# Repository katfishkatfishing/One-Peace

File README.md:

# One-Peace 🏴‍☠️
>Our plan for Third Space Hack Club - Week 2!

A locked box that refuses to open until brought to a specific geographic coordinate that can be determined through various puzzles.

ARG GitHub here:
[https://github.com/katfishkatfishing/Eye-of-God](https://github.com/katfishkatfishing/Eye-of-God)

## Overview
An arg inspired puzzle, alien-y sci-fi themed reverse geocache box. At first we started with the theme of treasure, then thought of geocaches. But those were already a thing, and we wanted our project to be unique so we did this reverse geocache, where you bring the box to the place then only it opens.
The ARG itself is cosmic horror themed.
To put it short, it's a box that only opens if you bring it to the specific coordinates (approximately).

### <ins>The Box</ins>
<ul style="margin-top: -5px; margin-bottom: 0; padding-left: 10px">
  <p style="margin-bottom: 5px">
    <b>GPS Tracking</b>
    <ul style="padding-left: 45px">
      <p style="text-indent: -24px; margin-bottom: 5px">
        <b>GPS Receiver Module:</b> An internal GPS receiver reads satellite signals to calculate latitude, longitude and keep track of its current location.</p>
      <p style="text-indent: -24px; margin-bottom: 5px">
        <b>Geofencing & Distance Logic:</b> The internal microcontroller runs algorithms to calculate the distance between the box's current coordinates and the pre-programmed target coordinates.</p>
      <p style="text-indent: -24px; margin-bottom: 20px">
        <b>Proximity Threshold:</b> The box opens once it is within a designated radius.</p>
    </ul>
  </p>
</ul>
<ul style="margin-top: 0; margin-bottom: 0; padding-left: 10px">
  <p style="margin-bottom: 5px">
    <b>Locking Mechanism</b>
    <ul style="padding-left: 45px">
      <p style="text-indent: -24px; margin-bottom: 5px">
        <b>Electronic Lock:</b> A motorized latch, driven by a micro servo motor that secures the lid mechanism.</p>
    </ul>
  </p>
</ul>
<ul style="margin-top: 0; margin-bottom: 0; padding-left: 10px">
  <p style="margin-bottom: 5px">
    <b>ARG Puzzle</b>
    <ul style="padding-left: 45px">
      <p style="text-indent: -24px; margin-bottom: 5px">
        <b>Puzzles!:</b> Clues that lead to more clues that lead to the destination, to witness the <i><b>"One Peace"</b></i> <i>(ps. the puzzles are ciphers)<i></p>
    </ul>
  </p>
</ul>

## PCB
Let's take a look at what is inside!
<table>
  <tr>
    <td align="center">
      Schematic<br>
      <br>
    </td>
    <td align="center">
      PCB Routing<br>
      <br>
    </td>
  </tr>
</table>

Now, let's take a look outside!
<table>
  <tr>
    <td align="center">
      <br>
    </td>
    <td align="center">
      <br>
    </td>
  </tr>
</table>

## BOM 💹
| Reference          | Qty | Value                         | DNP | Exclude from BOM | Exclude from Board | Footprint                                                                                  | Datasheet                                                                                            |
| ------------------ | --- | ----------------------------- | --- | ---------------- | ------------------ | ------------------------------------------------------------------------------------------ | ---------------------------------------------------------------------------------------------------- |
| C1                 | 1   | 470uF                         |     |                  |                    | Capacitor_Tantalum_SMD:CP_EIA-7343-43_Kemet-X_HandSolder                                   |                                                                                                      |
| C3,C9,C10          | 3   | 10uF                          |     |                  |                    | Capacitor_SMD:C_0603_1608Metric_Pad1.08x0.95mm_HandSolder                                  |                                                                                                      |
| C4,C7              | 2   | 0.1uF                         |     |                  |                    | Capacitor_SMD:C_0402_1005Metric_Pad0.74x0.62mm_HandSolder                                  |                                                                                                      |
| C5,C12,C13,C14,C15 | 5   | 22uF                          |     |                  |                    | Capacitor_SMD:C_0603_1608Metric_Pad1.08x0.95mm_HandSolder                                  |                                                                                                      |
| C6                 | 1   | 1uF                           |     |                  |                    | Capacitor_SMD:C_0603_1608Metric_Pad1.08x0.95mm_HandSolder                                  |                                                                                                      |
| C8                 | 1   | 100nF                         |     |                  |                    | Capacitor_SMD:C_0402_1005Metric_Pad0.74x0.62mm_HandSolder                                  |                                                                                                      |
| C11                | 1   | 10pF                          |     |                  |                    | Capacitor_SMD:C_0402_1005Metric_Pad0.74x0.62mm_HandSolder                                  |                                                                                                      |
| D3,D4,D5           | 3   | LED                           |     |                  |                    | LED_SMD:LED_0603_1608Metric_Pad1.05x0.95mm_HandSolder                                      |                                                                                                      |
| J1                 | 1   | USB_C_Receptacle_USB2.0_16P   |     |                  |                    | Connector_USB:USB_C_Receptacle_GCT_USB4085                                                 | https://www.usb.org/sites/default/files/documents/usb_type-c.zip                                     |
| J2                 | 1   | U.FL                          |     |                  |                    | U.FL_Molex_MCRF_73412-0110_Vertical:U.FL_Molex_MCRF_73412-0110_Vertical                    | https://wmsc.lcsc.com/wmsc/upload/file/pdf/v2/lcsc/2208151830_BAT-WIRELESS-BWU-FL-IPEX1_C5137195.pdf |
| J3                 | 1   | Conn_01x02                    |     |                  |                    | Connector_PinHeader_2.54mm:PinHeader_1x02_P2.54mm_Vertical                                 |                                                                                                      |
| L1                 | 1   | 1uH                           |     |                  |                    | Inductor_SMD:L_APV_ANR4030                                                                 |                                                                                                      |
| LCD1               | 1   | HS280S010B                    |     |                  |                    | lcsc_shared_footprints:C2939938_LCD-TH_HS280S010B                                          | https://wmsc.lcsc.com/wmsc/upload/file/pdf/v2/lcsc/2401291705_HS-HS280S010B_C2939938.pdf             |
| M1                 | 1   | Motor_Servo                   |     |                  |                    | Connector_PinHeader_2.54mm:PinHeader_1x03_P2.54mm_Vertical                                 | http://forums.parallax.com/uploads/attachments/46831/74481.png                                       |
| R6,R7,R8           | 3   | 470R                          |     |                  |                    | Resistor_SMD:R_0402_1005Metric_Pad0.72x0.64mm_HandSolder                                   |                                                                                                      |
| R9,R17             | 2   | 10k                           |     |                  |                    | Resistor_SMD:R_0603_1608Metric_Pad0.98x0.95mm_HandSolder                                   |                                                                                                      |
| R10                | 1   | 2k                            |     |                  |                    | Resistor_SMD:R_0603_1608Metric_Pad0.98x0.95mm_HandSolder                                   |                                                                                                      |
| R13,R14            | 2   | 5.1k                          |     |                  |                    | Resistor_SMD:R_0603_1608Metric_Pad0.98x0.95mm_HandSolder                                   |                                                                                                      |
| R18                | 1   | 0R                            |     |                  |                    | Resistor_SMD:R_0402_1005Metric_Pad0.72x0.64mm_HandSolder                                   |                                                                                                      |
| R19                | 1   | 1.6M                          |     |                  |                    | Resistor_SMD:R_0603_1608Metric_Pad0.98x0.95mm_HandSolder                                   |                                                                                                      |
| R20                | 1   | 39k                           |     |                  |                    | Resistor_SMD:R_0603_1608Metric_Pad0.98x0.95mm_HandSolder                                   |                                                                                                      |
| R21                | 1   | 1M                            |     |                  |                    | Resistor_SMD:R_0603_1608Metric                                                             |                                                                                                      |
| R22                | 1   | 180k                          |     |                  |                    | Resistor_SMD:R_0603_1608Metric_Pad0.98x0.95mm_HandSolder                                   |                                                                                                      |
| SW4                | 1   | SW_Push                       |     |                  |                    | Button_Switch_SMD:SW_SPST_B3U-1000P                                                        |                                                                                                      |
| U1                 | 1   | AMS1117-3.3                   |     |                  |                    | Package_TO_SOT_SMD:SOT-223-3_TabPin2                                                       | http://www.advanced-monolithic.com/pdf/ds1117.pdf                                                    |
| U2                 | 1   | NEO-6M-0-001_C32413118        |     |                  |                    | lcsc_shared_footprints:C32413118_SMD                                                       | None                                                                                                 |
| U3                 | 1   | TPS63020DSJR                  |     |                  |                    | lcsc_shared_footprints:C15483_VSON-14_L4_0-W3_0-P0_50-BL-EP_TI_DSJ                         | https://www.lcsc.com/datasheet/lcsc_datasheet_1809200040_Texas-Instruments-TPS63020DSJR_C15483.pdf   |
| U4                 | 1   | MCP73871-2CC                  |     |                  |                    | Package_DFN_QFN:QFN-20-1EP_4x4mm_P0.5mm_EP2.5x2.5mm                                        | http://www.mouser.com/ds/2/268/22090a-52174.pdf                                                      |
| U5                 | 1   | ESP32-S31-WROOM-3_C9900281993 |     |                  |                    | lcsc_shared_footprints:C9900281993_COMM-SMD_99P-L33_0-W26_0-P0_85_ESP32-S31-MINI-1-H16R16V | None                                                                                                 |

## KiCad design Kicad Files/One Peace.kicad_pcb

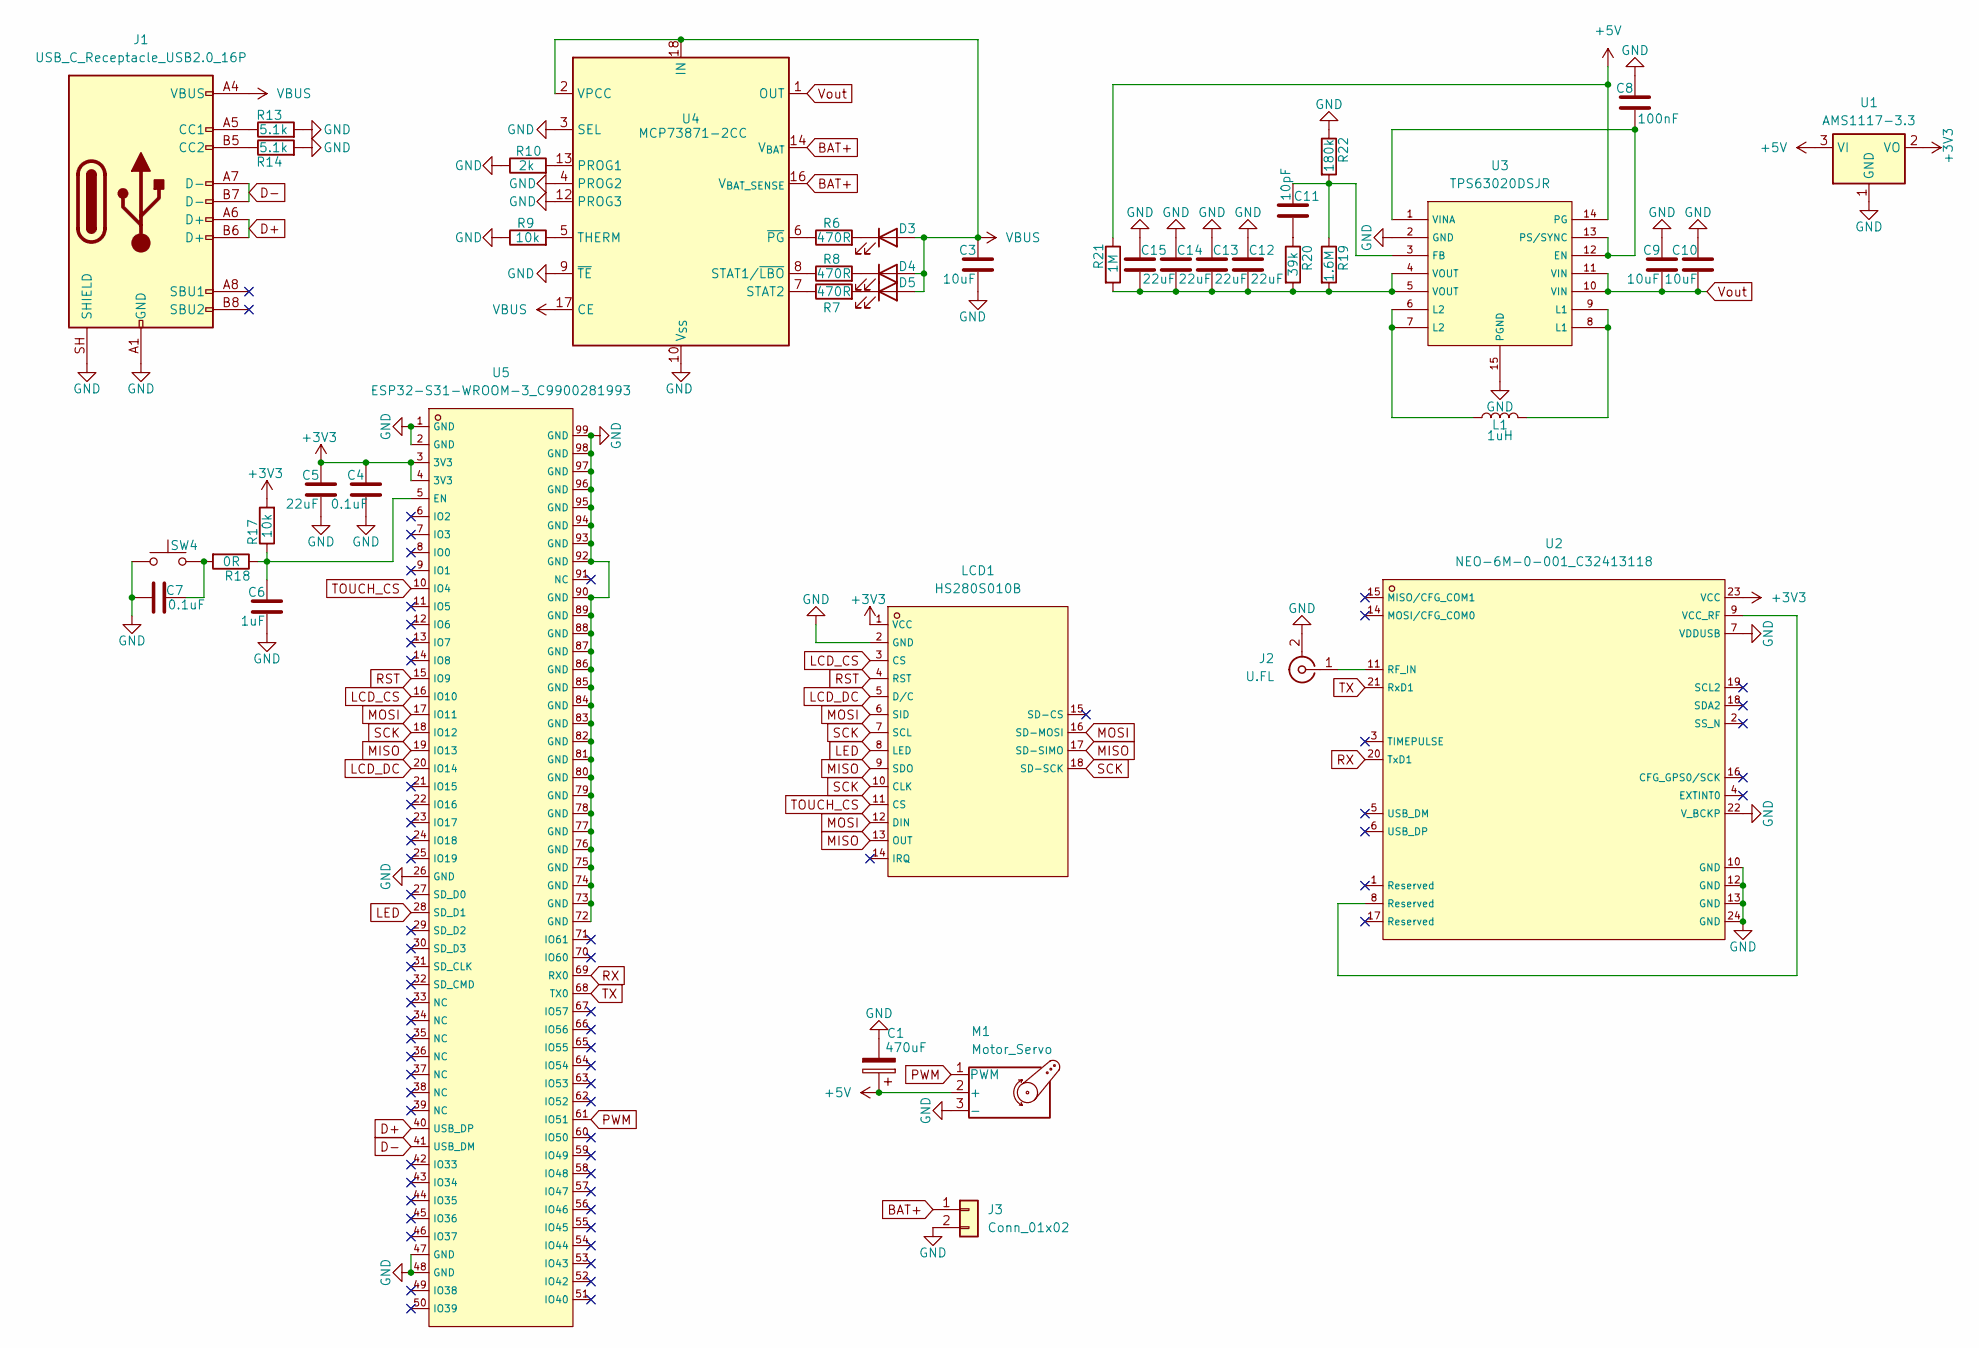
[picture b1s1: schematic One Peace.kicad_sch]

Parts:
C1: 470uF; CP_EIA-7343-43_Kemet-X_HandSolder
C3, C9, C10: 10uF; C_0603_1608Metric_Pad1.08x0.95mm_HandSolder
C4, C7: 0.1uF; C_0402_1005Metric_Pad0.74x0.62mm_HandSolder
C5, C12, C13, C14, C15: 22uF; C_0603_1608Metric_Pad1.08x0.95mm_HandSolder
C6: 1uF; C_0603_1608Metric_Pad1.08x0.95mm_HandSolder
C8: 100nF; C_0402_1005Metric_Pad0.74x0.62mm_HandSolder
C11: 10pF; C_0402_1005Metric_Pad0.74x0.62mm_HandSolder
D3, D4, D5: LED; LED_0603_1608Metric_Pad1.05x0.95mm_HandSolder
J1: USB_C_Receptacle_USB2.0_16P; USB_C_Receptacle_GCT_USB4085
J2: U.FL; U.FL_Molex_MCRF_73412-0110_Vertical; LCSC C5137195
J3: Conn_01x02; PinHeader_1x02_P2.54mm_Vertical
L1: 1uH; L_APV_ANR4030
LCD1: HS280S010B; C2939938_LCD-TH_HS280S010B; LCSC C2939938
M1: Motor_Servo; PinHeader_1x03_P2.54mm_Vertical
R6, R7, R8: 470R; R_0402_1005Metric_Pad0.72x0.64mm_HandSolder
R9, R17: 10k; R_0603_1608Metric_Pad0.98x0.95mm_HandSolder
R10: 2k; R_0603_1608Metric_Pad0.98x0.95mm_HandSolder
R13, R14: 5.1k; R_0603_1608Metric_Pad0.98x0.95mm_HandSolder
R18: 0R; R_0402_1005Metric_Pad0.72x0.64mm_HandSolder
R19: 1.6M; R_0603_1608Metric_Pad0.98x0.95mm_HandSolder
R20: 39k; R_0603_1608Metric_Pad0.98x0.95mm_HandSolder
R21: 1M; R_0603_1608Metric
R22: 180k; R_0603_1608Metric_Pad0.98x0.95mm_HandSolder
SW4: SW_Push; SW_SPST_B3U-1000P
U1: AMS1117-3.3; SOT-223-3_TabPin2
U2: NEO-6M-0-001_C32413118; C32413118_SMD; LCSC C32413118
U3: TPS63020DSJR; C15483_VSON-14_L4_0-W3_0-P0_50-BL-EP_TI_DSJ; LCSC C15483
U4: MCP73871-2CC; QFN-20-1EP_4x4mm_P0.5mm_EP2.5x2.5mm
U5: ESP32-S31-WROOM-3_C9900281993; C9900281993_COMM-SMD_99P-L33_0-W26_0-P0_85_ESP32-S31-MINI-1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; LCSC C9900281993

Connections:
+3V3: C4.1, C5.1, LCD1.1 (VCC), R17.2, U1.2 (VO), U2.23 (VCC), U5.3 (3V3), U5.4 (3V3)
+5V: C1.1, M1.2 (+), R21.1, U1.3 (VI), U3.14 (PG)
BAT+: J3.1, U4.14 (V_{BAT}), U4.15 (V_{BAT}), U4.16 (V_{BAT_SENSE})
D+: J1.A6 (D+), J1.B6 (D+), U5.40 (USB_DP)
D-: J1.A7 (D-), J1.B7 (D-), U5.41 (USB_DM)
GND: C1.2, C3.2, C4.2, C5.2, C6.2, C7.1, C8.1, C9.1, C10.1, C12.1, C13.1, C14.1, C15.1, J1.A1 (GND), J1.A12 (GND), J1.B1 (GND), J1.B12 (GND), J1.SH (SHIELD), J2.2 (Ext), J3.2, LCD1.2 (GND), M1.3 (-), R9.1, R10.1, R13.2, R14.2, R22.1, SW4.2, U1.1 (GND), U2.7 (VDDUSB), U2.10 (GND), U2.12 (GND), U2.13 (GND), U2.22 (V_BCKP), U2.24 (GND), U3.2 (GND), U3.15 (PGND), U4.3 (SEL), U4.4 (PROG2), U4.9 (~TE), U4.10 (V_{SS}), U4.11 (V_{SS}), U4.12 (PROG3), U4.21 (V_{SS}), U5.1 (GND), U5.2 (GND), U5.26 (GND), U5.47 (GND), U5.48 (GND), U5.72 (GND), U5.73 (GND), U5.74 (GND), U5.75 (GND), U5.76 (GND), U5.77 (GND), U5.78 (GND), U5.79 (GND), U5.80 (GND), U5.81 (GND), U5.82 (GND), U5.83 (GND), U5.84 (GND), U5.85 (GND), U5.86 (GND), U5.87 (GND), U5.88 (GND), U5.89 (GND), U5.90 (GND), U5.92 (GND), U5.93 (GND), U5.94 (GND), U5.95 (GND), U5.96 (GND), U5.97 (GND), U5.98 (GND), U5.99 (GND)
LCD_CS: LCD1.3 (CS), U5.16 (IO10)
LCD_DC: LCD1.5 (D/C), U5.20 (IO14)
LED: LCD1.8 (LED), U5.28 (SD_D1)
MISO: LCD1.9 (SDO), LCD1.13 (OUT), LCD1.17 (SD-SIMO), U5.19 (IO13)
MOSI: LCD1.6 (SID), LCD1.12 (DIN), LCD1.16 (SD-MOSI), U5.17 (IO11)
unnamed: C7.2, R18.2, SW4.1
unnamed: C11.2, R20.1
unnamed: C12.2, C13.2, C14.2, C15.2, R19.2, R20.2, R21.2, U3.4 (VOUT), U3.5 (VOUT)
unnamed: D3.1 (K), R6.2
unnamed: D4.1 (K), R8.2
unnamed: D5.1 (K), R7.2
unnamed: J1.A5 (CC1), R13.1
unnamed: J1.B5 (CC2), R14.1
unnamed: J2.1 (In), U2.11 (RF_IN)
unnamed: L1.1, U3.6 (L2), U3.7 (L2)
unnamed: L1.2, U3.8 (L1), U3.9 (L1)
unnamed: U2.8 (Reserved), U2.9 (VCC_RF)
unnamed: C8.2, U3.1 (VINA), U3.12 (EN), U3.13 (PS/SYNC)
unnamed: C11.1, R19.1, R22.2, U3.3 (FB)
unnamed: R10.2, U4.13 (PROG1)
unnamed: R8.1, U4.8 (STAT1/~LBO)
unnamed: R7.1, U4.7 (STAT2)
unnamed: R9.2, U4.5 (THERM)
unnamed: R6.1, U4.6 (~PG)
unnamed: C6.1, R17.1, R18.1, U5.5 (EN)
PWM: M1.1 (PWM), U5.61 (IO51)
RST: LCD1.4 (RST), U5.15 (IO9)
RX: U2.20 (TxD1), U5.69 (RX0)
SCK: LCD1.7 (SCL), LCD1.10 (CLK), LCD1.18 (SD-SCK), U5.18 (IO12)
TOUCH_CS: LCD1.11 (CS), U5.10 (IO4)
TX: U2.21 (RxD1), U5.68 (TX0)
VBUS: C3.1, D3.2 (A), D4.2 (A), D5.2 (A), J1.A4 (VBUS), J1.A9 (VBUS), J1.B4 (VBUS), J1.B9 (VBUS), U4.2 (VPCC), U4.17 (CE), U4.18 (IN), U4.19 (IN)
Vout: C9.2, C10.2, U3.10 (VIN), U3.11 (VIN), U4.1 (OUT), U4.20 (OUT)

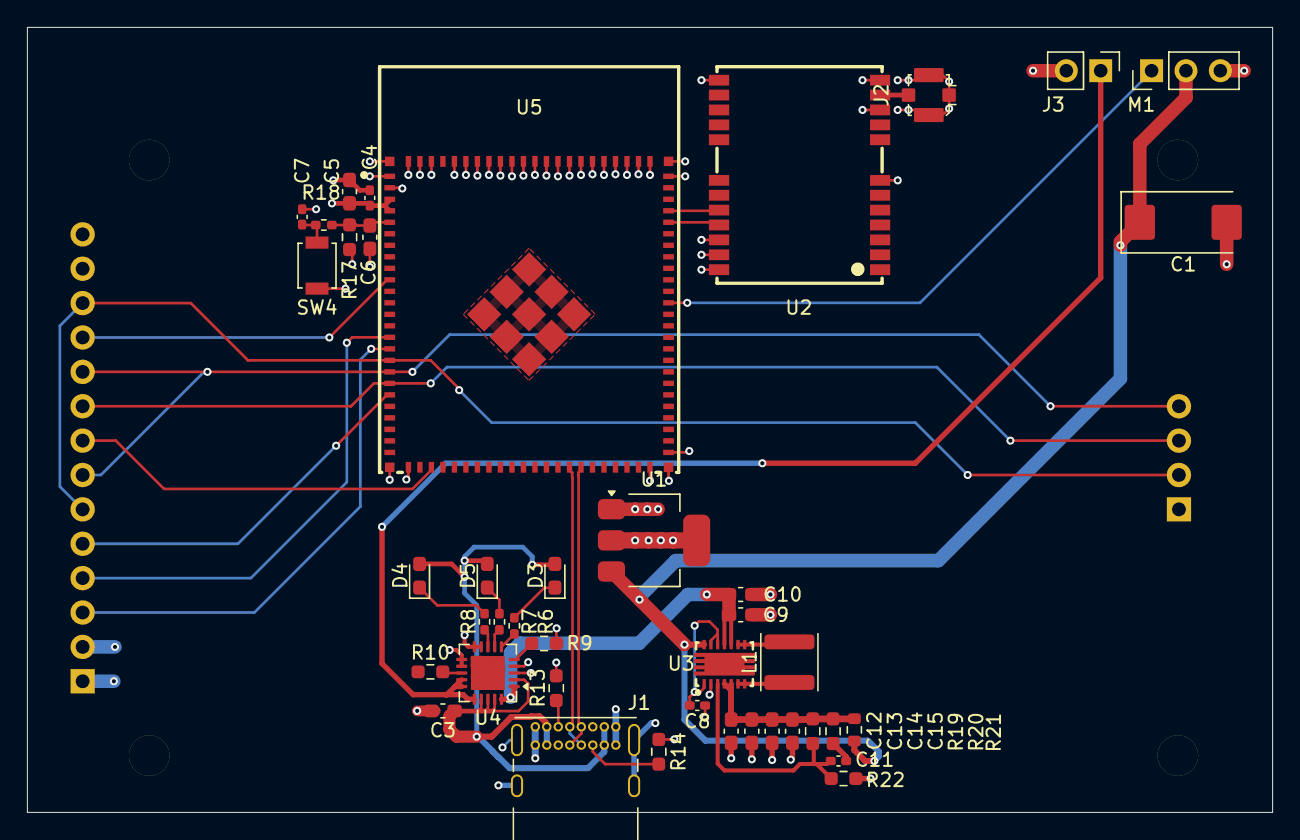
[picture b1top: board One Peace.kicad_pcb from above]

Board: 4 copper layers, 92.0 x 58.0 mm, 42 parts (1 on the bottom side), 39 nets.

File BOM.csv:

"Reference","Qty","Value","DNP","Exclude from BOM","Exclude from Board","Footprint","Datasheet"
"C1","1","470uF","","","","Capacitor_Tantalum_SMD:CP_EIA-7343-43_Kemet-X_HandSolder",""
"C3,C9,C10","3","10uF","","","","Capacitor_SMD:C_0603_1608Metric_Pad1.08x0.95mm_HandSolder",""
"C4,C7","2","0.1uF","","","","Capacitor_SMD:C_0402_1005Metric_Pad0.74x0.62mm_HandSolder",""
"C5,C12,C13,C14,C15","5","22uF","","","","Capacitor_SMD:C_0603_1608Metric_Pad1.08x0.95mm_HandSolder",""
"C6","1","1uF","","","","Capacitor_SMD:C_0603_1608Metric_Pad1.08x0.95mm_HandSolder",""
"C8","1","100nF","","","","Capacitor_SMD:C_0402_1005Metric_Pad0.74x0.62mm_HandSolder",""
"C11","1","10pF","","","","Capacitor_SMD:C_0402_1005Metric_Pad0.74x0.62mm_HandSolder",""
"D3,D4,D5","3","LED","","","","LED_SMD:LED_0603_1608Metric_Pad1.05x0.95mm_HandSolder",""
"J1","1","USB_C_Receptacle_USB2.0_16P","","","","Connector_USB:USB_C_Receptacle_GCT_USB4085","https://www.usb.org/sites/default/files/documents/usb_type-c.zip"
"J2","1","U.FL","","","","U.FL_Molex_MCRF_73412-0110_Vertical:U.FL_Molex_MCRF_73412-0110_Vertical","https://wmsc.lcsc.com/wmsc/upload/file/pdf/v2/lcsc/220815183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"
"J3","1","Conn_01x02","","","","Connector_PinHeader_2.54mm:PinHeader_1x02_P2.54mm_Vertical",""
"L1","1","1uH","","","","Inductor_SMD:L_APV_ANR4030",""
"LCD1","1","HS280S010B","","","","lcsc_shared_footprints:C2939938_LCD-TH_HS280S010B","https://wmsc.lcsc.com/wmsc/upload/file/pdf/v2/lcsc/240129170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"
"M1","1","Motor_Servo","","","","Connector_PinHeader_2.54mm:PinHeader_1x03_P2.54mm_Vertical","http://forums.parallax.com/uploads/attachments/46831/74481.png"
"R6,R7,R8","3","470R","","","","Resistor_SMD:R_0402_1005Metric_Pad0.72x0.64mm_HandSolder",""
"R9,R17","2","10k","","","","Resistor_SMD:R_0603_1608Metric_Pad0.98x0.95mm_HandSolder",""
"R10","1","2k","","","","Resistor_SMD:R_0603_1608Metric_Pad0.98x0.95mm_HandSolder",""
"R13,R14","2","5.1k","","","","Resistor_SMD:R_0603_1608Metric_Pad0.98x0.95mm_HandSolder",""
"R18","1","0R","","","","Resistor_SMD:R_0402_1005Metric_Pad0.72x0.64mm_HandSolder",""
"R19","1","1.6M","","","","Resistor_SMD:R_0603_1608Metric_Pad0.98x0.95mm_HandSolder",""
"R20","1","39k","","","","Resistor_SMD:R_0603_1608Metric_Pad0.98x0.95mm_HandSolder",""
"R21","1","1M","","","","Resistor_SMD:R_0603_1608Metric",""
"R22","1","180k","","","","Resistor_SMD:R_0603_1608Metric_Pad0.98x0.95mm_HandSolder",""
"SW4","1","SW_Push","","","","Button_Switch_SMD:SW_SPST_B3U-1000P",""
"U1","1","AMS1117-3.3","","","","Package_TO_SOT_SMD:SOT-223-3_TabPin2","http://www.advanced-monolithic.com/pdf/ds1117.pdf"
"U2","1","NEO-6M-0-001_C32413118","","","","lcsc_shared_footprints:C32413118_SMD","None"
"U3","1","TPS63020DSJR","","","","lcsc_shared_footprints:C15483_VSON-14_L4_0-W3_0-P0_50-BL-EP_TI_DSJ","https://www.lcsc.com/datasheet/lcsc_datasheet_1809200040_Tex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"
"U4","1","MCP73871-2CC","","","","Package_DFN_QFN:QFN-20-1EP_4x4mm_P0.5mm_EP2.5x2.5mm","http://www.mouser.com/ds/2/268/22090a-52174.pdf"
"U5","1","ESP32-S31-WROOM-3_C9900281993","","","","lcsc_shared_footprints:C9900281993_COMM-SMD_99P-L33_0-W26_0-P0_85_ESP32-S31-MINI-1-H16R16V","None"
